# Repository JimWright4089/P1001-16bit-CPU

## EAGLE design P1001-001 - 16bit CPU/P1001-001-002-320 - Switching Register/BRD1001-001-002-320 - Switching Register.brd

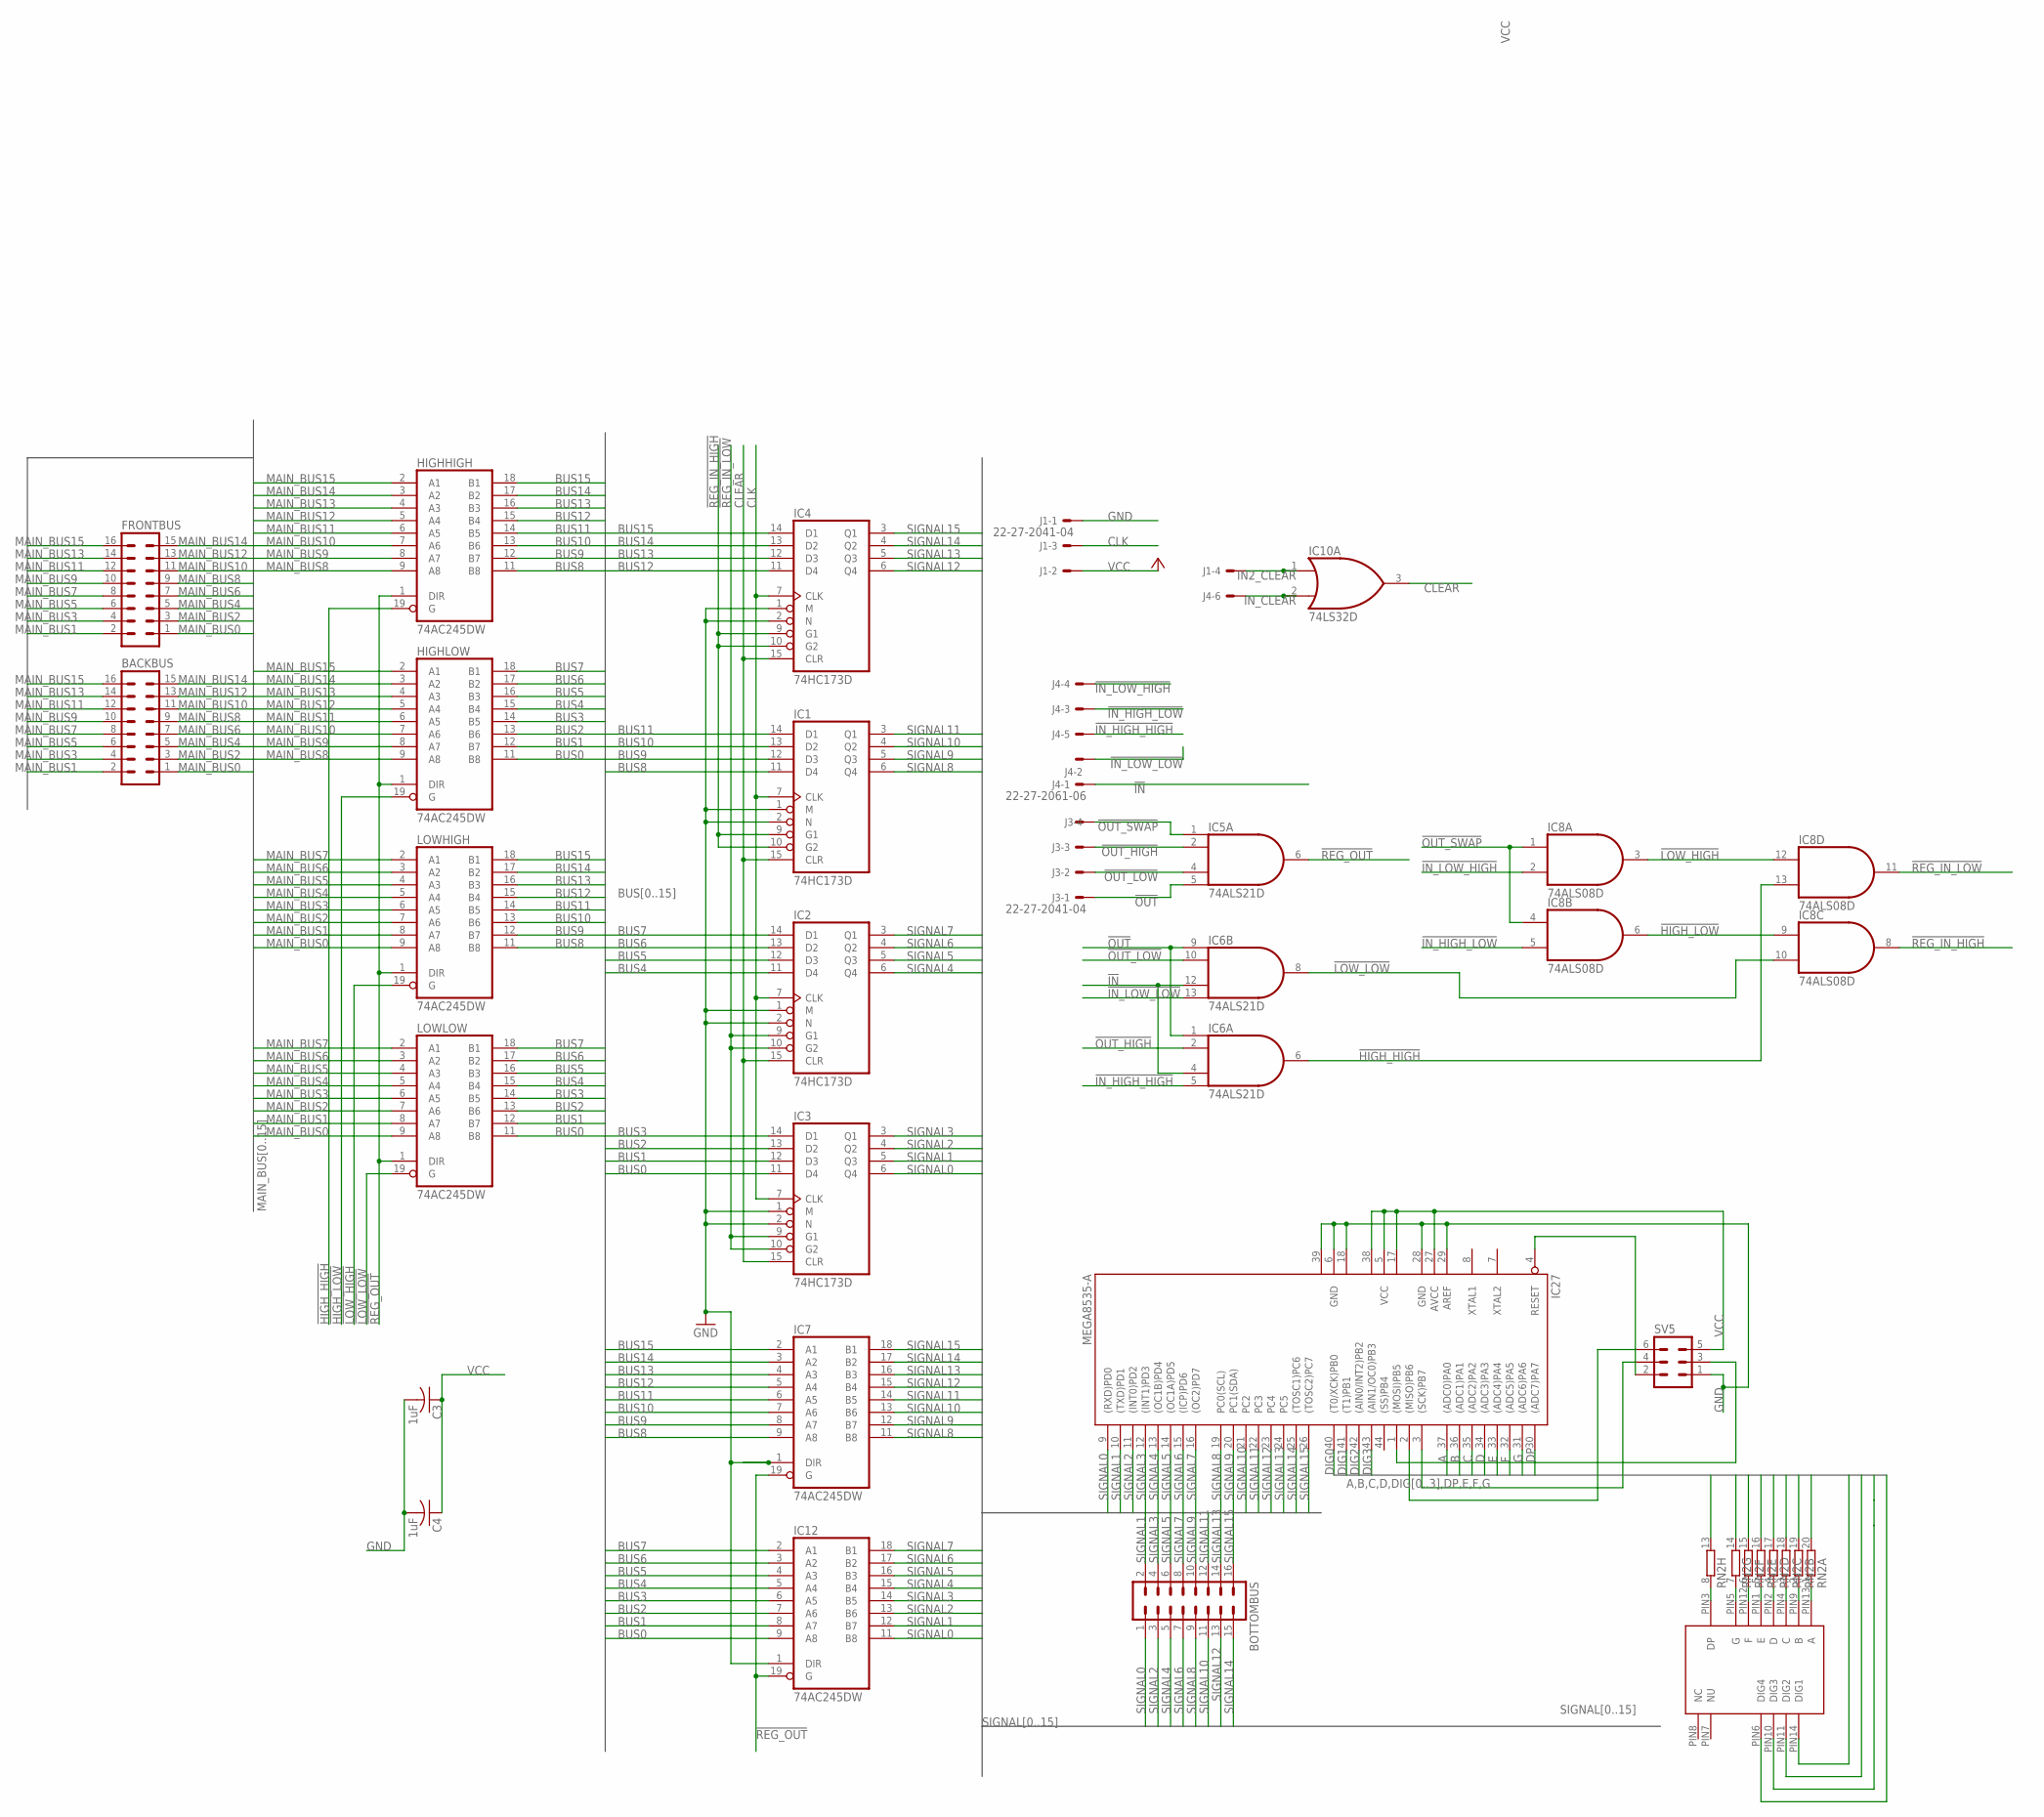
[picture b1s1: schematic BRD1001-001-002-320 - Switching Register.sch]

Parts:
BACKBUS: ML16
BOTTOMBUS: ML16
C3, C4: 1uF; C1206
FRONTBUS: ML16
HIGHHIGH: 74AC245DW; SO20W
HIGHLOW: 74AC245DW; SO20W
IC1, IC2, IC3, IC4: 74HC173D; SO16
IC5, IC6: 74ALS21D; SO14
IC7, IC12: 74AC245DW; SO20W
IC8: 74ALS08D; SO14
IC10: 74LS32D; SO14
IC27: MEGA8535-A; TQFP44
J1, J3: 22-27-2041-04; 6410-04
J4: 22-27-2061-06; 6410-06
LOWHIGH: 74AC245DW; SO20W
LOWLOW: 74AC245DW; SO20W
RN2: 10R-NSOMC; SOMC20
SV5: ML6
U$1: 4-DIGIT-7-SEGMENT

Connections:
!HIGH_HIGH: HIGHHIGH.19 (G), IC6.6 (O), IC8.13 (I1)
!HIGH_LOW: HIGHLOW.19 (G), IC8.6 (O), IC8.9 (I0)
!IN: IC6.4 (I2), IC6.12 (I2), J4.1
!IN_HIGH_HIGH: IC6.5 (I3), J4.5
!IN_HIGH_LOW: IC8.5 (I1), J4.3
!IN_LOW_HIGH: IC8.2 (I1), J4.4
!IN_LOW_LOW: IC6.13 (I3), J4.2
!LOW_HIGH: IC8.3 (O), IC8.12 (I0), LOWHIGH.19 (G)
!LOW_LOW: IC6.8 (O), IC8.10 (I1), LOWLOW.19 (G)
!OUT: IC5.5 (I3), IC6.1 (I0), IC6.9 (I0), J3.1
!OUT_HIGH: IC5.2 (I1), IC6.2 (I1), J3.3
!OUT_LOW: IC5.4 (I2), IC6.10 (I1), J3.2
!OUT_SWAP: IC5.1 (I0), IC8.1 (I0), IC8.4 (I0), J3.4
!REG_IN_HIGH: IC1.9 (G1), IC1.10 (G2), IC4.9 (G1), IC4.10 (G2), IC8.8 (O)
!REG_IN_LOW: IC2.9 (G1), IC2.10 (G2), IC3.9 (G1), IC3.10 (G2), IC8.11 (O)
!REG_OUT: HIGHHIGH.1 (DIR), HIGHLOW.1 (DIR), IC5.6 (O), IC7.19 (G), IC12.19 (G), LOWHIGH.1 (DIR), LOWLOW.1 (DIR)
A: IC27.37 ((ADC0)PA0), RN2.20 (2)
B: IC27.36 ((ADC1)PA1), RN2.19 (2)
BUS0: HIGHLOW.11 (B8), IC3.11 (D4), IC12.9 (A8), LOWLOW.11 (B8)
BUS1: HIGHLOW.12 (B7), IC3.12 (D3), IC12.8 (A7), LOWLOW.12 (B7)
BUS2: HIGHLOW.13 (B6), IC3.13 (D2), IC12.7 (A6), LOWLOW.13 (B6)
BUS3: HIGHLOW.14 (B5), IC3.14 (D1), IC12.6 (A5), LOWLOW.14 (B5)
BUS4: HIGHLOW.15 (B4), IC2.11 (D4), IC12.5 (A4), LOWLOW.15 (B4)
BUS5: HIGHLOW.16 (B3), IC2.12 (D3), IC12.4 (A3), LOWLOW.16 (B3)
BUS6: HIGHLOW.17 (B2), IC2.13 (D2), IC12.3 (A2), LOWLOW.17 (B2)
BUS7: HIGHLOW.18 (B1), IC2.14 (D1), IC12.2 (A1), LOWLOW.18 (B1)
BUS8: HIGHHIGH.11 (B8), IC1.11 (D4), IC7.9 (A8), LOWHIGH.11 (B8)
BUS9: HIGHHIGH.12 (B7), IC1.12 (D3), IC7.8 (A7), LOWHIGH.12 (B7)
BUS10: HIGHHIGH.13 (B6), IC1.13 (D2), IC7.7 (A6), LOWHIGH.13 (B6)
BUS11: HIGHHIGH.14 (B5), IC1.14 (D1), IC7.6 (A5), LOWHIGH.14 (B5)
BUS12: HIGHHIGH.15 (B4), IC4.11 (D4), IC7.5 (A4), LOWHIGH.15 (B4)
BUS13: HIGHHIGH.16 (B3), IC4.12 (D3), IC7.4 (A3), LOWHIGH.16 (B3)
BUS14: HIGHHIGH.17 (B2), IC4.13 (D2), IC7.3 (A2), LOWHIGH.17 (B2)
BUS15: HIGHHIGH.18 (B1), IC4.14 (D1), IC7.2 (A1), LOWHIGH.18 (B1)
C: IC27.35 ((ADC2)PA2), RN2.18 (2)
CLEAR: IC1.15 (CLR), IC2.15 (CLR), IC3.15 (CLR), IC4.15 (CLR), IC10.3 (O)
CLK: IC1.7 (CLK), IC2.7 (CLK), IC3.7 (CLK), IC4.7 (CLK), J1.3
D: IC27.34 ((ADC3)PA3), RN2.17 (2)
DIG0: IC27.40 ((T0/XCK)PB0), U$1.PIN14 (DIG1)
DIG1: IC27.41 ((T1)PB1), U$1.PIN11 (DIG2)
DIG2: IC27.42 ((AIN0/INT2)PB2), U$1.PIN10 (DIG3)
DIG3: IC27.43 ((AIN1/OC0)PB3), U$1.PIN6 (DIG4)
DP: IC27.30 ((ADC7)PA7), RN2.13 (2)
E: IC27.33 ((ADC4)PA4), RN2.16 (2)
F: IC27.32 ((ADC5)PA5), RN2.15 (2)
G: IC27.31 ((ADC6)PA6), RN2.14 (2)
GND: C3.2, C4.2, HIGHHIGH.10 (GND), HIGHLOW.10 (GND), IC1.1 (M), IC1.2 (N), IC1.8 (GND), IC2.1 (M), IC2.2 (N), IC2.8 (GND), IC3.1 (M), IC3.2 (N), IC3.8 (GND), IC4.1 (M), IC4.2 (N), IC4.8 (GND), IC5.7 (GND), IC6.7 (GND), IC7.1 (DIR), IC7.10 (GND), IC8.7 (GND), IC10.7 (GND), IC12.1 (DIR), IC12.10 (GND), IC27.6 (GND), IC27.18 (GND1), IC27.28 (GND), IC27.29 (AREF), IC27.39 (GND2), J1.1, LOWHIGH.10 (GND), LOWLOW.10 (GND), SV5.1
IN2_CLEAR: IC10.1 (I0), J1.4
IN_CLEAR: IC10.2 (I1), J4.6
MAIN_BUS0: BACKBUS.1, FRONTBUS.1, LOWHIGH.9 (A8), LOWLOW.9 (A8)
MAIN_BUS1: BACKBUS.2, FRONTBUS.2, LOWHIGH.8 (A7), LOWLOW.8 (A7)
MAIN_BUS2: BACKBUS.3, FRONTBUS.3, LOWHIGH.7 (A6), LOWLOW.7 (A6)
MAIN_BUS3: BACKBUS.4, FRONTBUS.4, LOWHIGH.6 (A5), LOWLOW.6 (A5)
MAIN_BUS4: BACKBUS.5, FRONTBUS.5, LOWHIGH.5 (A4), LOWLOW.5 (A4)
MAIN_BUS5: BACKBUS.6, FRONTBUS.6, LOWHIGH.4 (A3), LOWLOW.4 (A3)
MAIN_BUS6: BACKBUS.7, FRONTBUS.7, LOWHIGH.3 (A2), LOWLOW.3 (A2)
MAIN_BUS7: BACKBUS.8, FRONTBUS.8, LOWHIGH.2 (A1), LOWLOW.2 (A1)
MAIN_BUS8: BACKBUS.9, FRONTBUS.9, HIGHHIGH.9 (A8), HIGHLOW.9 (A8)
MAIN_BUS9: BACKBUS.10, FRONTBUS.10, HIGHHIGH.8 (A7), HIGHLOW.8 (A7)
MAIN_BUS10: BACKBUS.11, FRONTBUS.11, HIGHHIGH.7 (A6), HIGHLOW.7 (A6)
MAIN_BUS11: BACKBUS.12, FRONTBUS.12, HIGHHIGH.6 (A5), HIGHLOW.6 (A5)
MAIN_BUS12: BACKBUS.13, FRONTBUS.13, HIGHHIGH.5 (A4), HIGHLOW.5 (A4)
MAIN_BUS13: BACKBUS.14, FRONTBUS.14, HIGHHIGH.4 (A3), HIGHLOW.4 (A3)
MAIN_BUS14: BACKBUS.15, FRONTBUS.15, HIGHHIGH.3 (A2), HIGHLOW.3 (A2)
MAIN_BUS15: BACKBUS.16, FRONTBUS.16, HIGHHIGH.2 (A1), HIGHLOW.2 (A1)
unnamed: IC27.1 ((MOSI)PB5), SV5.3
unnamed: IC27.3 ((SCK)PB7), SV5.4
unnamed: IC27.2 ((MISO)PB6), SV5.6
unnamed: IC27.4 (RESET), SV5.2
unnamed: RN2.1, U$1.PIN13 (A)
unnamed: RN2.2 (1), U$1.PIN9 (B)
unnamed: RN2.3 (1), U$1.PIN4 (C)
unnamed: RN2.4 (1), U$1.PIN2 (D)
unnamed: RN2.5 (1), U$1.PIN1 (E)
unnamed: RN2.6 (1), U$1.PIN12 (F)
unnamed: RN2.7 (1), U$1.PIN5 (G)
unnamed: RN2.8 (1), U$1.PIN3 (DP)
SIGNAL0: BOTTOMBUS.1, IC3.6 (Q4), IC12.11 (B8), IC27.9 ((RXD)PD0)
SIGNAL1: BOTTOMBUS.2, IC3.5 (Q3), IC12.12 (B7), IC27.10 ((TXD)PD1)
SIGNAL2: BOTTOMBUS.3, IC3.4 (Q2), IC12.13 (B6), IC27.11 ((INT0)PD2)
SIGNAL3: BOTTOMBUS.4, IC3.3 (Q1), IC12.14 (B5), IC27.12 ((INT1)PD3)
SIGNAL4: BOTTOMBUS.5, IC2.6 (Q4), IC12.15 (B4), IC27.13 ((OC1B)PD4)
SIGNAL5: BOTTOMBUS.6, IC2.5 (Q3), IC12.16 (B3), IC27.14 ((OC1A)PD5)
SIGNAL6: BOTTOMBUS.7, IC2.4 (Q2), IC12.17 (B2), IC27.15 ((ICP)PD6)
SIGNAL7: BOTTOMBUS.8, IC2.3 (Q1), IC12.18 (B1), IC27.16 ((OC2)PD7)
SIGNAL8: BOTTOMBUS.9, IC1.6 (Q4), IC7.11 (B8), IC27.19 (PC0(SCL))
SIGNAL9: BOTTOMBUS.10, IC1.5 (Q3), IC7.12 (B7), IC27.20 (PC1(SDA))
SIGNAL10: BOTTOMBUS.11, IC1.4 (Q2), IC7.13 (B6), IC27.21 (PC2)
SIGNAL11: BOTTOMBUS.12, IC1.3 (Q1), IC7.14 (B5), IC27.22 (PC3)
SIGNAL12: BOTTOMBUS.13, IC4.6 (Q4), IC7.15 (B4), IC27.23 (PC4)
SIGNAL13: BOTTOMBUS.14, IC4.5 (Q3), IC7.16 (B3), IC27.24 (PC5)
SIGNAL14: BOTTOMBUS.15, IC4.4 (Q2), IC7.17 (B2), IC27.25 ((TOSC1)PC6)
SIGNAL15: BOTTOMBUS.16, IC4.3 (Q1), IC7.18 (B1), IC27.26 ((TOSC2)PC7)
VCC: C3.1, C4.1, HIGHHIGH.20 (VCC), HIGHLOW.20 (VCC), IC1.16 (VCC), IC2.16 (VCC), IC3.16 (VCC), IC4.16 (VCC), IC5.14 (VCC), IC6.14 (VCC), IC7.20 (VCC), IC8.14 (VCC), IC10.14 (VCC), IC12.20 (VCC), IC27.5 (VCC), IC27.17 (VCC1), IC27.27 (AVCC), IC27.38 (VCC2), J1.2, LOWHIGH.20 (VCC), LOWLOW.20 (VCC), SV5.5

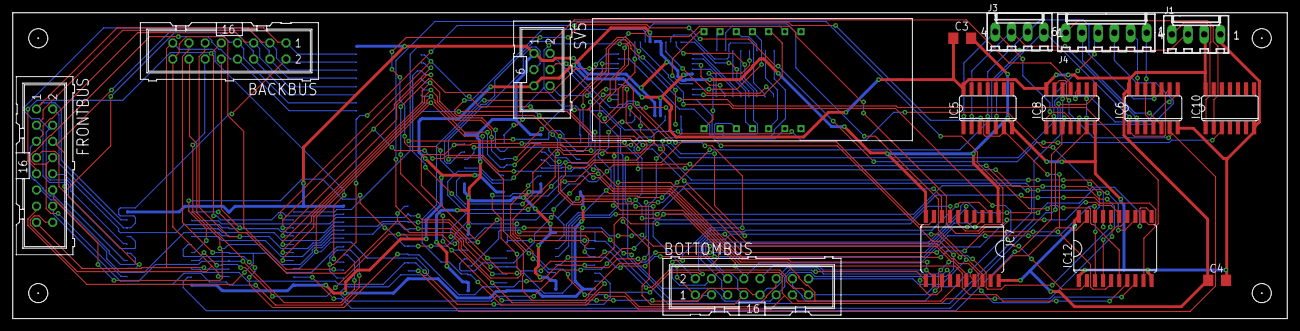
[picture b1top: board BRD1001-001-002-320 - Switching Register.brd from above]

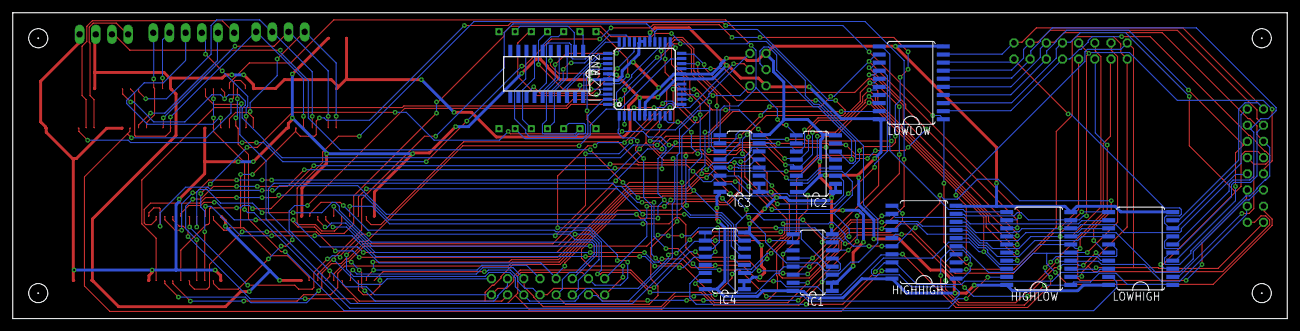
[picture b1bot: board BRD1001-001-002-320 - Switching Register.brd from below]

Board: 2 copper layers, 200.0 x 48.0 mm, 26 parts (10 on the bottom side), 94 nets.

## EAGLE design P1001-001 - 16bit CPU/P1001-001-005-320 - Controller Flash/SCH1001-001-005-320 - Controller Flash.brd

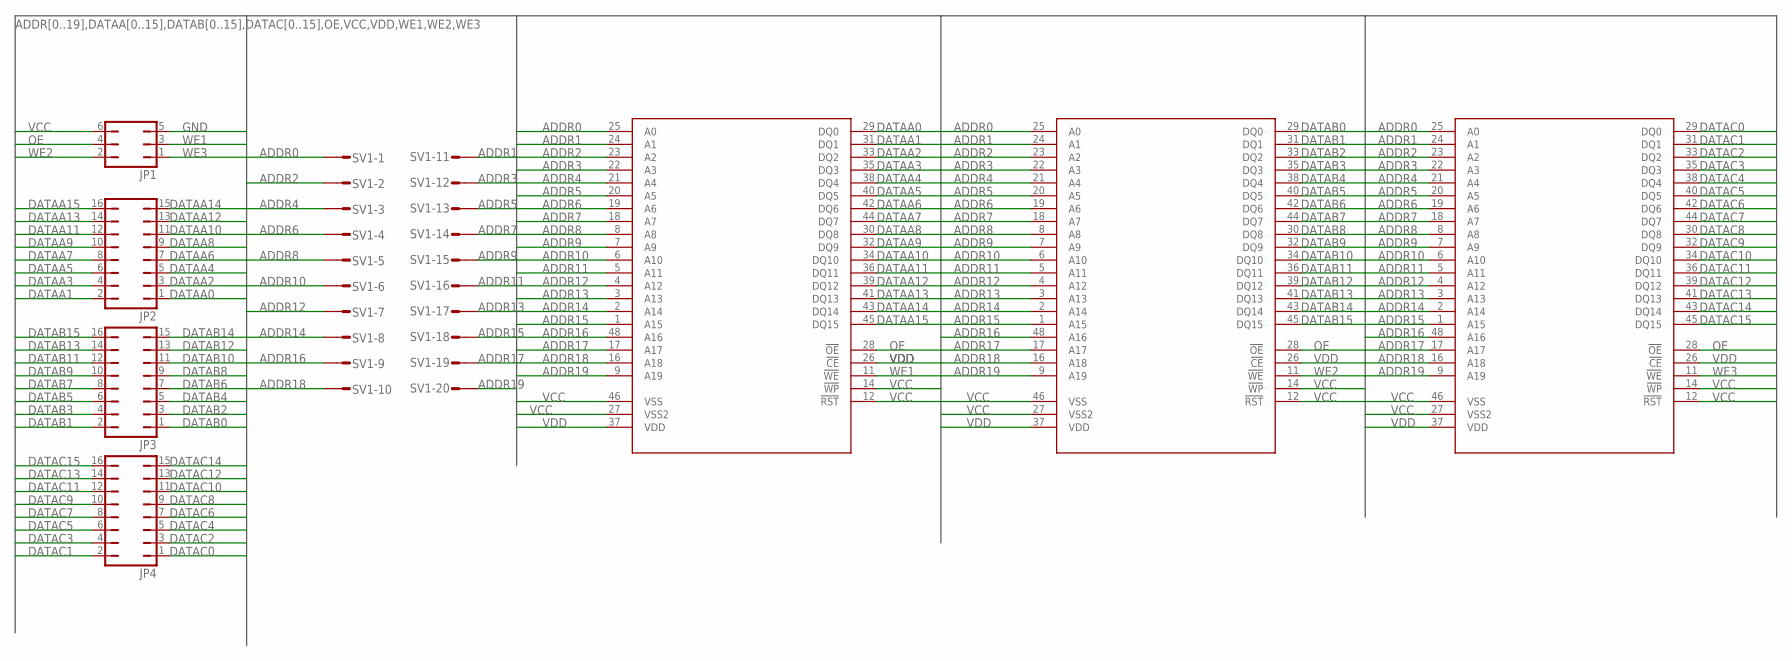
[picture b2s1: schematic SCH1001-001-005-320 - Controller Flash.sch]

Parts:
JP1: JP3Q
JP2, JP3, JP4: JP8Q
SV1: S20P
U$1, U$2, U$3: SST39VF1602-70-4I-EKE; TSOP48

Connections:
ADDR0: SV1.1, U$1.25 (A0), U$2.25 (A0), U$3.25 (A0)
ADDR1: SV1.11, U$1.24 (A1), U$2.24 (A1), U$3.24 (A1)
ADDR2: SV1.2, U$1.23 (A2), U$2.23 (A2), U$3.23 (A2)
ADDR3: SV1.12, U$1.22 (A3), U$2.22 (A3), U$3.22 (A3)
ADDR4: SV1.3, U$1.21 (A4), U$2.21 (A4), U$3.21 (A4)
ADDR5: SV1.13, U$1.20 (A5), U$2.20 (A5), U$3.20 (A5)
ADDR6: SV1.4, U$1.19 (A6), U$2.19 (A6), U$3.19 (A6)
ADDR7: SV1.14, U$1.18 (A7), U$2.18 (A7), U$3.18 (A7)
ADDR8: SV1.5, U$1.8 (A8), U$2.8 (A8), U$3.8 (A8)
ADDR9: SV1.15, U$1.7 (A9), U$2.7 (A9), U$3.7 (A9)
ADDR10: SV1.6, U$1.6 (A10), U$2.6 (A10), U$3.6 (A10)
ADDR11: SV1.16, U$1.5 (A11), U$2.5 (A11), U$3.5 (A11)
ADDR12: SV1.7, U$1.4 (A12), U$2.4 (A12), U$3.4 (A12)
ADDR13: SV1.17, U$1.3 (A13), U$2.3 (A13), U$3.3 (A13)
ADDR14: SV1.8, U$1.2 (A14), U$2.2 (A14), U$3.2 (A14)
ADDR15: SV1.18, U$1.1 (A15), U$2.1 (A15), U$3.1 (A15)
ADDR16: SV1.9, U$1.48 (A16), U$2.48 (A16), U$3.48 (A16)
ADDR17: SV1.19, U$1.17 (A17), U$2.17 (A17), U$3.17 (A17)
ADDR18: SV1.10, U$1.16 (A18), U$2.16 (A18), U$3.16 (A18)
ADDR19: SV1.20, U$1.9 (A19), U$2.9 (A19), U$3.9 (A19)
DATAA0: JP2.1, U$1.29 (DQ0)
DATAA1: JP2.2, U$1.31 (DQ1)
DATAA2: JP2.3, U$1.33 (DQ2)
DATAA3: JP2.4, U$1.35 (DQ3)
DATAA4: JP2.5, U$1.38 (DQ4)
DATAA5: JP2.6, U$1.40 (DQ5)
DATAA6: JP2.7, U$1.42 (DQ6)
DATAA7: JP2.8, U$1.44 (DQ7)
DATAA8: JP2.9, U$1.30 (DQ8)
DATAA9: JP2.10, U$1.32 (DQ9)
DATAA10: JP2.11, U$1.34 (DQ10)
DATAA11: JP2.12, U$1.36 (DQ11)
DATAA12: JP2.13, U$1.39 (DQ12)
DATAA13: JP2.14, U$1.41 (DQ13)
DATAA14: JP2.15, U$1.43 (DQ14)
DATAA15: JP2.16, U$1.45 (DQ15)
DATAB0: JP3.1, U$2.29 (DQ0)
DATAB1: JP3.2, U$2.31 (DQ1)
DATAB2: JP3.3, U$2.33 (DQ2)
DATAB3: JP3.4, U$2.35 (DQ3)
DATAB4: JP3.5, U$2.38 (DQ4)
DATAB5: JP3.6, U$2.40 (DQ5)
DATAB6: JP3.7, U$2.42 (DQ6)
DATAB7: JP3.8, U$2.44 (DQ7)
DATAB8: JP3.9, U$2.30 (DQ8)
DATAB9: JP3.10, U$2.32 (DQ9)
DATAB10: JP3.11, U$2.34 (DQ10)
DATAB11: JP3.12, U$2.36 (DQ11)
DATAB12: JP3.13, U$2.39 (DQ12)
DATAB13: JP3.14, U$2.41 (DQ13)
DATAB14: JP3.15, U$2.43 (DQ14)
DATAB15: JP3.16, U$2.45 (DQ15)
DATAC0: JP4.1, U$3.29 (DQ0)
DATAC1: JP4.2, U$3.31 (DQ1)
DATAC2: JP4.3, U$3.33 (DQ2)
DATAC3: JP4.4, U$3.35 (DQ3)
DATAC4: JP4.5, U$3.38 (DQ4)
DATAC5: JP4.6, U$3.40 (DQ5)
DATAC6: JP4.7, U$3.42 (DQ6)
DATAC7: JP4.8, U$3.44 (DQ7)
DATAC8: JP4.9, U$3.30 (DQ8)
DATAC9: JP4.10, U$3.32 (DQ9)
DATAC10: JP4.11, U$3.34 (DQ10)
DATAC11: JP4.12, U$3.36 (DQ11)
DATAC12: JP4.13, U$3.39 (DQ12)
DATAC13: JP4.14, U$3.41 (DQ13)
DATAC14: JP4.15, U$3.43 (DQ14)
DATAC15: JP4.16, U$3.45 (DQ15)
GND: JP1.5
OE: JP1.4, U$1.28 (!OE), U$2.28 (!OE), U$3.28 (!OE)
VCC: JP1.6, U$1.12 (!RST), U$1.14 (!WP), U$1.27 (VSS2), U$1.46 (VSS), U$2.12 (!RST), U$2.14 (!WP), U$2.27 (VSS2), U$2.46 (VSS), U$3.12 (!RST), U$3.14 (!WP), U$3.27 (VSS2), U$3.46 (VSS)
VDD: U$1.26 (!CE), U$1.37 (VDD), U$2.26 (!CE), U$2.37 (VDD), U$3.26 (!CE), U$3.37 (VDD)
WE1: JP1.3, U$1.11 (!WE)
WE2: JP1.2, U$2.11 (!WE)
WE3: JP1.1, U$3.11 (!WE)

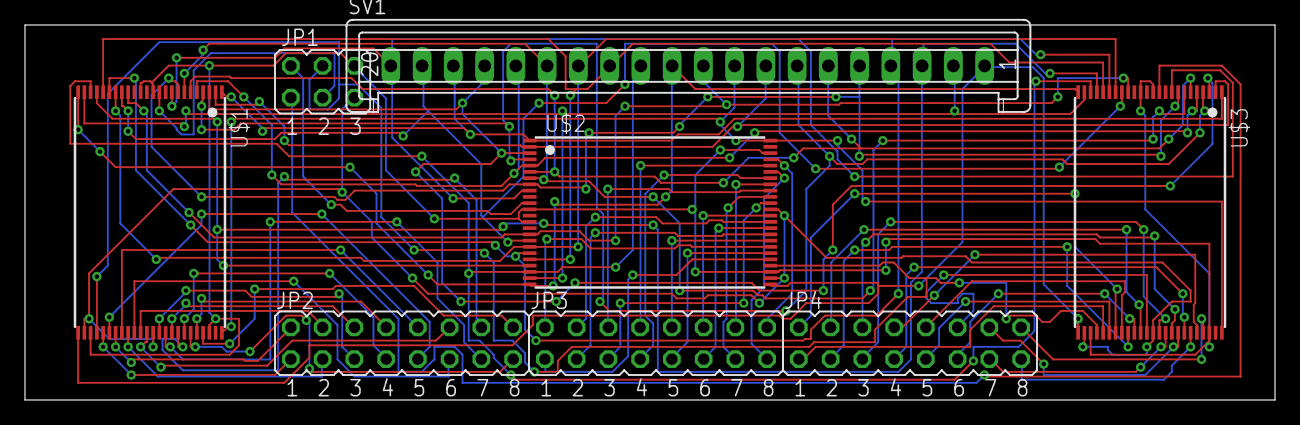
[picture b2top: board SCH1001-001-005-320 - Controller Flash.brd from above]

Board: 2 copper layers, 100.0 x 30.0 mm, 8 parts (0 on the bottom side), 74 nets.

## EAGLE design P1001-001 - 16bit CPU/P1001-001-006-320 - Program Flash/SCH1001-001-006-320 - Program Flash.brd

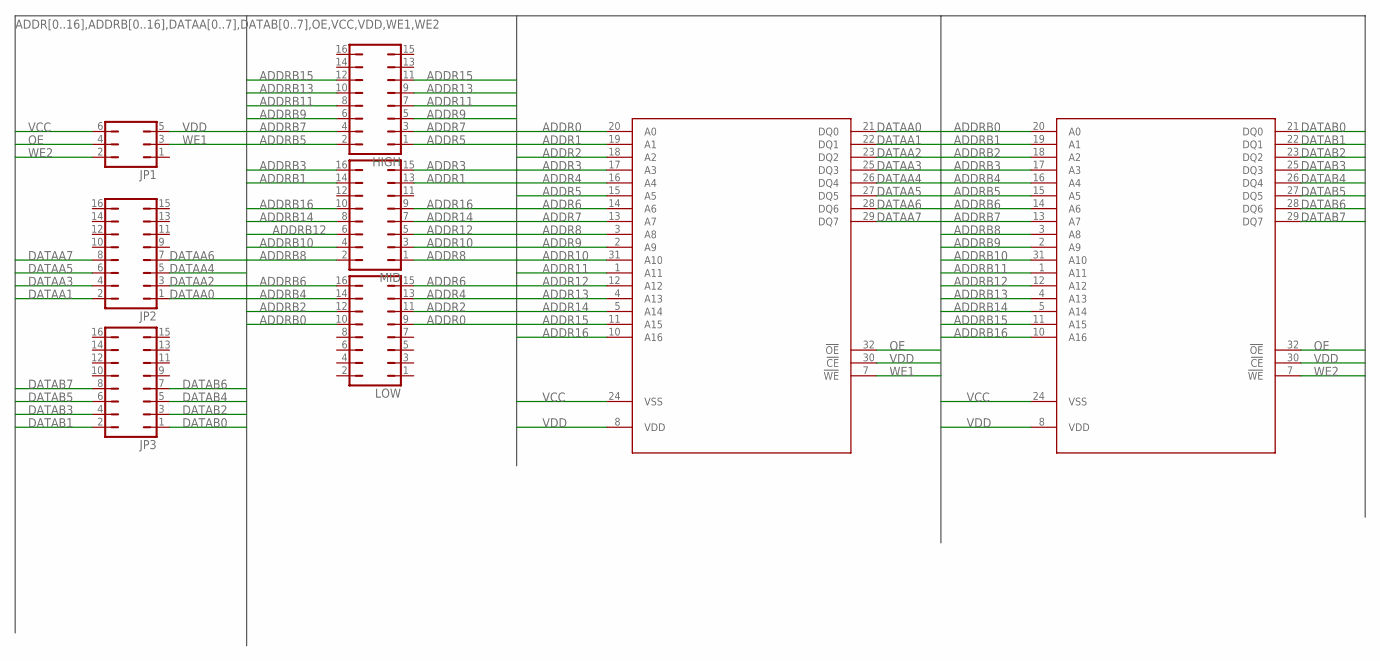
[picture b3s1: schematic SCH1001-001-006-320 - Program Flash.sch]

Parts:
HIGH: JP8Q
JP1: JP3Q
JP2, JP3: JP8Q
LOW: JP8Q
MID: JP8Q
U$1, U$2: PROGRAMFLASH; TSOP32

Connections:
ADDR0: LOW.9, U$1.20 (A0)
ADDR1: MID.13, U$1.19 (A1)
ADDR2: LOW.11, U$1.18 (A2)
ADDR3: MID.15, U$1.17 (A3)
ADDR4: LOW.13, U$1.16 (A4)
ADDR5: HIGH.1, U$1.15 (A5)
ADDR6: LOW.15, U$1.14 (A6)
ADDR7: HIGH.3, U$1.13 (A7)
ADDR8: MID.1, U$1.3 (A8)
ADDR9: HIGH.5, U$1.2 (A9)
ADDR10: MID.3, U$1.31 (A10)
ADDR11: HIGH.7, U$1.1 (A11)
ADDR12: MID.5, U$1.12 (A12)
ADDR13: HIGH.9, U$1.4 (A13)
ADDR14: MID.7, U$1.5 (A14)
ADDR15: HIGH.11, U$1.11 (A15)
ADDR16: MID.9, U$1.10 (A16)
ADDRB0: LOW.10, U$2.20 (A0)
ADDRB1: MID.14, U$2.19 (A1)
ADDRB2: LOW.12, U$2.18 (A2)
ADDRB3: MID.16, U$2.17 (A3)
ADDRB4: LOW.14, U$2.16 (A4)
ADDRB5: HIGH.2, U$2.15 (A5)
ADDRB6: LOW.16, U$2.14 (A6)
ADDRB7: HIGH.4, U$2.13 (A7)
ADDRB8: MID.2, U$2.3 (A8)
ADDRB9: HIGH.6, U$2.2 (A9)
ADDRB10: MID.4, U$2.31 (A10)
ADDRB11: HIGH.8, U$2.1 (A11)
ADDRB12: MID.6, U$2.12 (A12)
ADDRB13: HIGH.10, U$2.4 (A13)
ADDRB14: MID.8, U$2.5 (A14)
ADDRB15: HIGH.12, U$2.11 (A15)
ADDRB16: MID.10, U$2.10 (A16)
DATAA0: JP2.1, U$1.21 (DQ0)
DATAA1: JP2.2, U$1.22 (DQ1)
DATAA2: JP2.3, U$1.23 (DQ2)
DATAA3: JP2.4, U$1.25 (DQ3)
DATAA4: JP2.5, U$1.26 (DQ4)
DATAA5: JP2.6, U$1.27 (DQ5)
DATAA6: JP2.7, U$1.28 (DQ6)
DATAA7: JP2.8, U$1.29 (DQ7)
DATAB0: JP3.1, U$2.21 (DQ0)
DATAB1: JP3.2, U$2.22 (DQ1)
DATAB2: JP3.3, U$2.23 (DQ2)
DATAB3: JP3.4, U$2.25 (DQ3)
DATAB4: JP3.5, U$2.26 (DQ4)
DATAB5: JP3.6, U$2.27 (DQ5)
DATAB6: JP3.7, U$2.28 (DQ6)
DATAB7: JP3.8, U$2.29 (DQ7)
OE: JP1.4, U$1.32 (!OE), U$2.32 (!OE)
VCC: JP1.6, U$1.24 (VSS), U$2.24 (VSS)
VDD: JP1.5, U$1.8 (VDD), U$1.30 (!CE), U$2.8 (VDD), U$2.30 (!CE)
WE1: JP1.3, U$1.7 (!WE)
WE2: JP1.2, U$2.7 (!WE)

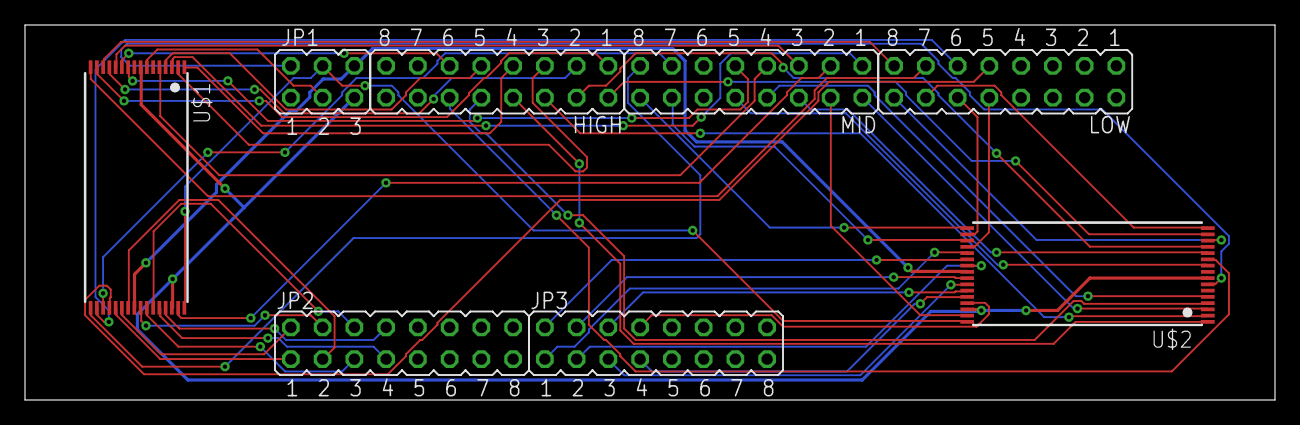
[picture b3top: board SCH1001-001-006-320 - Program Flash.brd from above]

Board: 2 copper layers, 100.0 x 30.0 mm, 8 parts (0 on the bottom side), 55 nets.

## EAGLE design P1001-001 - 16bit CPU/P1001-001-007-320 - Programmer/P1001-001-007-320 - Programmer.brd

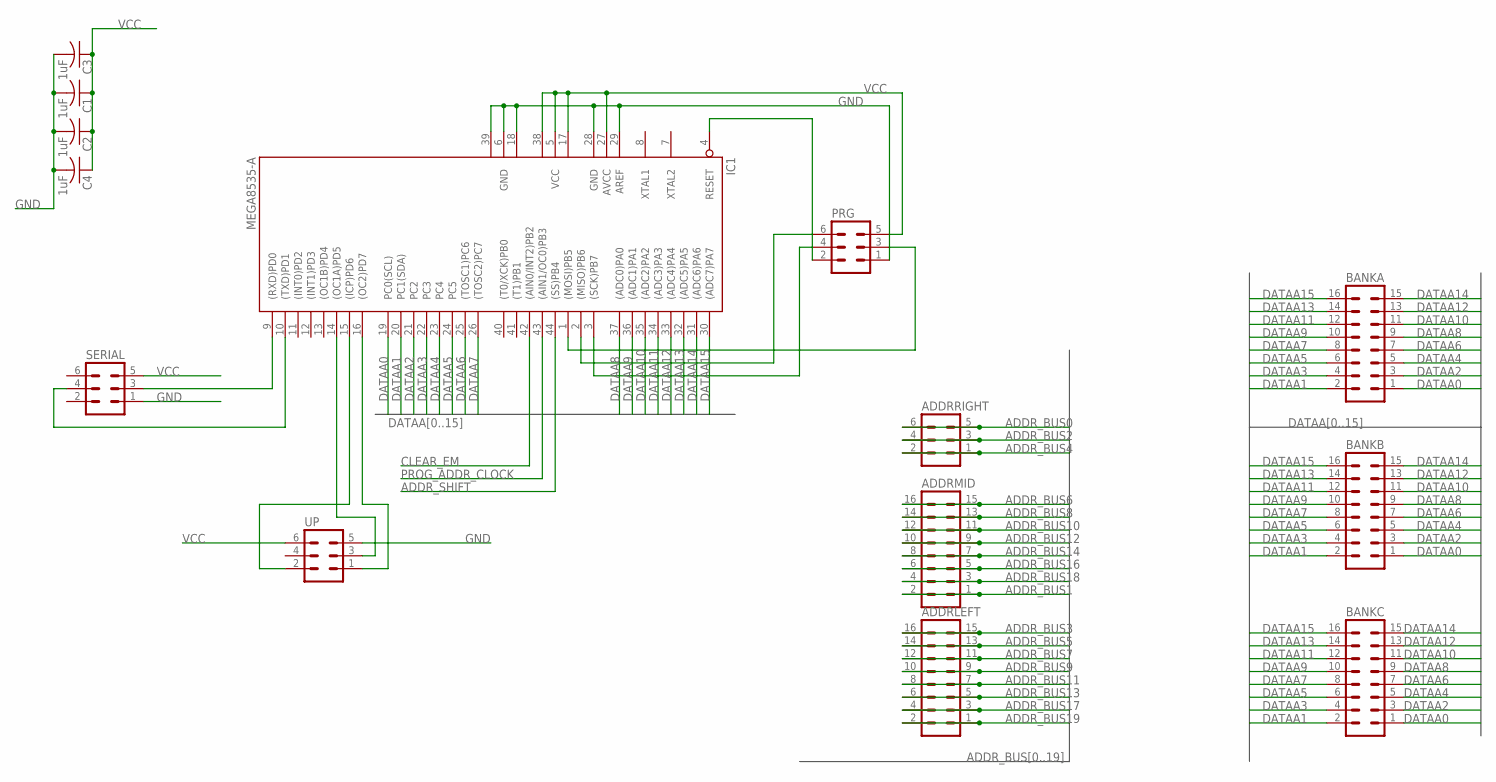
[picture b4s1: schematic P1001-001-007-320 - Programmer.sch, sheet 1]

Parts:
ADDRLEFT: ML16
ADDRMID: ML16
ADDRRIGHT: ML6
BANKA: ML16
BANKB: ML16
BANKC: ML16
C1, C2, C3, C4: 1uF; C1206
IC1: MEGA8535-A; TQFP44
PRG: ML6
SERIAL: ML6
UP: ML6

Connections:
ADDR_BUS0: ADDRRIGHT.5, ADDRRIGHT.6; also elsewhere on the board
ADDR_BUS1: ADDRMID.1, ADDRMID.2; also elsewhere on the board
ADDR_BUS2: ADDRRIGHT.3, ADDRRIGHT.4; also elsewhere on the board
ADDR_BUS3: ADDRLEFT.15, ADDRLEFT.16; also elsewhere on the board
ADDR_BUS4: ADDRRIGHT.1, ADDRRIGHT.2; also elsewhere on the board
ADDR_BUS5: ADDRLEFT.13, ADDRLEFT.14; also elsewhere on the board
ADDR_BUS6: ADDRMID.15, ADDRMID.16; also elsewhere on the board
ADDR_BUS7: ADDRLEFT.11, ADDRLEFT.12; also elsewhere on the board
ADDR_BUS8: ADDRMID.13, ADDRMID.14; also elsewhere on the board
ADDR_BUS9: ADDRLEFT.9, ADDRLEFT.10; also elsewhere on the board
ADDR_BUS10: ADDRMID.11, ADDRMID.12; also elsewhere on the board
ADDR_BUS11: ADDRLEFT.7, ADDRLEFT.8; also elsewhere on the board
ADDR_BUS12: ADDRMID.9, ADDRMID.10; also elsewhere on the board
ADDR_BUS13: ADDRLEFT.5, ADDRLEFT.6; also elsewhere on the board
ADDR_BUS14: ADDRMID.7, ADDRMID.8; also elsewhere on the board
ADDR_BUS16: ADDRMID.5, ADDRMID.6; also elsewhere on the board
ADDR_BUS17: ADDRLEFT.3, ADDRLEFT.4; also elsewhere on the board
ADDR_BUS18: ADDRMID.3, ADDRMID.4; also elsewhere on the board
ADDR_BUS19: ADDRLEFT.1, ADDRLEFT.2; also elsewhere on the board
ADDR_SHIFT: IC1.44 ((SS)PB4); also elsewhere on the board
CLEAR_EM: IC1.42 ((AIN0/INT2)PB2); also elsewhere on the board
DATAA0: BANKA.1, BANKB.1, BANKC.1, IC1.19 (PC0(SCL))
DATAA1: BANKA.2, BANKB.2, BANKC.2, IC1.20 (PC1(SDA))
DATAA2: BANKA.3, BANKB.3, BANKC.3, IC1.21 (PC2)
DATAA3: BANKA.4, BANKB.4, BANKC.4, IC1.22 (PC3)
DATAA4: BANKA.5, BANKB.5, BANKC.5, IC1.23 (PC4)
DATAA5: BANKA.6, BANKB.6, BANKC.6, IC1.24 (PC5)
DATAA6: BANKA.7, BANKB.7, BANKC.7, IC1.25 ((TOSC1)PC6)
DATAA7: BANKA.8, BANKB.8, BANKC.8, IC1.26 ((TOSC2)PC7)
DATAA8: BANKA.9, BANKB.9, BANKC.9, IC1.37 ((ADC0)PA0)
DATAA9: BANKA.10, BANKB.10, BANKC.10, IC1.36 ((ADC1)PA1)
DATAA10: BANKA.11, BANKB.11, BANKC.11, IC1.35 ((ADC2)PA2)
DATAA11: BANKA.12, BANKB.12, BANKC.12, IC1.34 ((ADC3)PA3)
DATAA12: BANKA.13, BANKB.13, BANKC.13, IC1.33 ((ADC4)PA4)
DATAA13: BANKA.14, BANKB.14, BANKC.14, IC1.32 ((ADC5)PA5)
DATAA14: BANKA.15, BANKB.15, BANKC.15, IC1.31 ((ADC6)PA6)
DATAA15: BANKA.16, BANKB.16, BANKC.16, IC1.30 ((ADC7)PA7)
GND: C1.2, C2.2, C3.2, C4.2, IC1.6 (GND), IC1.18 (GND1), IC1.28 (GND), IC1.29 (AREF), IC1.39 (GND2), PRG.1, SERIAL.1, UP.5; also elsewhere on the board
unnamed: IC1.14 ((OC1A)PD5), UP.3
unnamed: IC1.1 ((MOSI)PB5), PRG.3
unnamed: IC1.3 ((SCK)PB7), PRG.4
unnamed: IC1.2 ((MISO)PB6), PRG.6
unnamed: IC1.4 (RESET), PRG.2
unnamed: IC1.16 ((OC2)PD7), UP.1
unnamed: IC1.9 ((RXD)PD0), SERIAL.3
unnamed: IC1.10 ((TXD)PD1), SERIAL.4
unnamed: IC1.15 ((ICP)PD6), UP.2
PROG_ADDR_CLOCK: IC1.43 ((AIN1/OC0)PB3); also elsewhere on the board
VCC: C1.1, C2.1, C3.1, C4.1, IC1.5 (VCC), IC1.17 (VCC1), IC1.27 (AVCC), IC1.38 (VCC2), PRG.5, SERIAL.5, UP.6; also elsewhere on the board

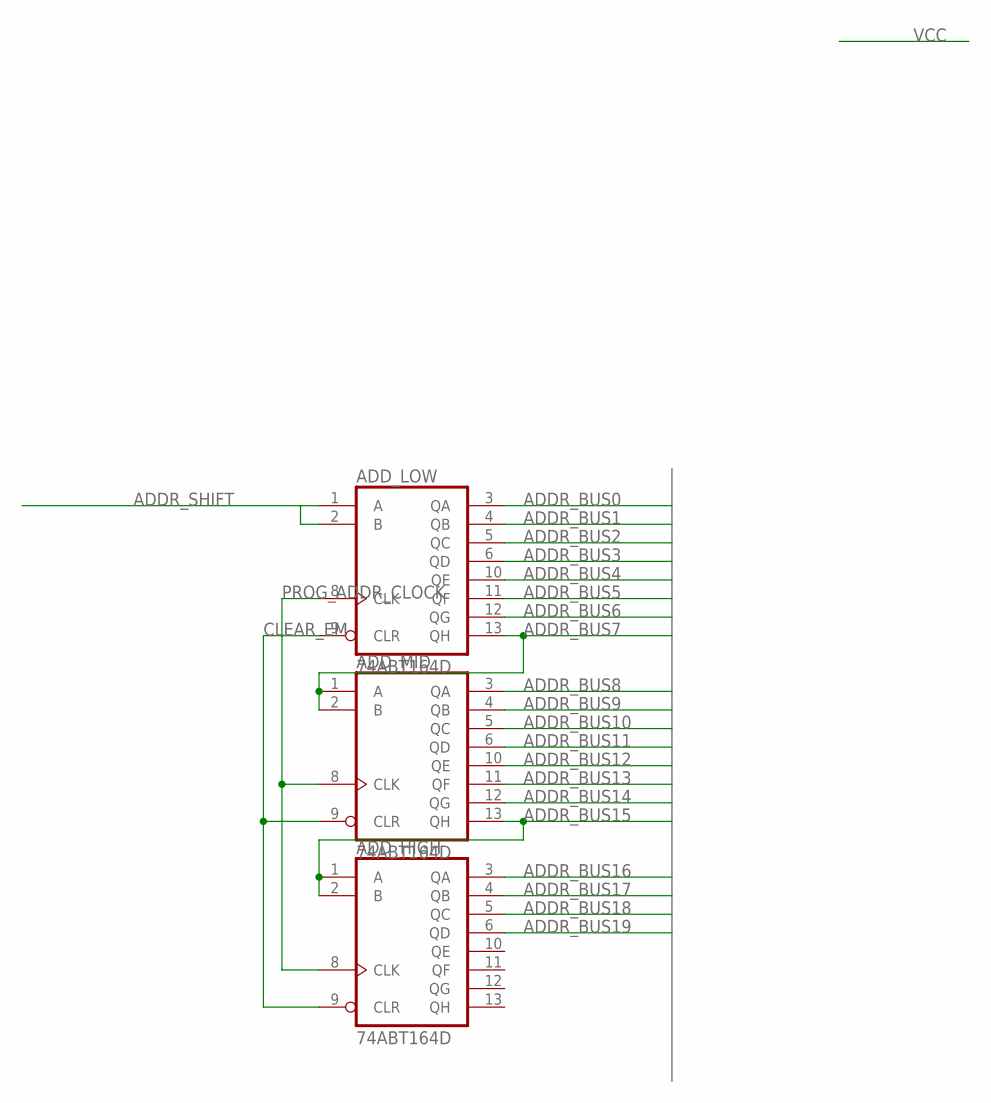
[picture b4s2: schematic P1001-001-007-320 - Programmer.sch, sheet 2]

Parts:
ADD_HIGH: 74ABT164D; SO14
ADD_LOW: 74ABT164D; SO14
ADD_MID: 74ABT164D; SO14

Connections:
ADDR_BUS0: ADD_LOW.3 (QA); also elsewhere on the board
ADDR_BUS1: ADD_LOW.4 (QB); also elsewhere on the board
ADDR_BUS2: ADD_LOW.5 (QC); also elsewhere on the board
ADDR_BUS3: ADD_LOW.6 (QD); also elsewhere on the board
ADDR_BUS4: ADD_LOW.10 (QE); also elsewhere on the board
ADDR_BUS5: ADD_LOW.11 (QF); also elsewhere on the board
ADDR_BUS6: ADD_LOW.12 (QG); also elsewhere on the board
ADDR_BUS7: ADD_LOW.13 (QH), ADD_MID.1 (A), ADD_MID.2 (B); also elsewhere on the board
ADDR_BUS8: ADD_MID.3 (QA); also elsewhere on the board
ADDR_BUS9: ADD_MID.4 (QB); also elsewhere on the board
ADDR_BUS10: ADD_MID.5 (QC); also elsewhere on the board
ADDR_BUS11: ADD_MID.6 (QD); also elsewhere on the board
ADDR_BUS12: ADD_MID.10 (QE); also elsewhere on the board
ADDR_BUS13: ADD_MID.11 (QF); also elsewhere on the board
ADDR_BUS14: ADD_MID.12 (QG); also elsewhere on the board
ADDR_BUS15: ADD_HIGH.1 (A), ADD_HIGH.2 (B), ADD_MID.13 (QH)
ADDR_BUS16: ADD_HIGH.3 (QA); also elsewhere on the board
ADDR_BUS17: ADD_HIGH.4 (QB); also elsewhere on the board
ADDR_BUS18: ADD_HIGH.5 (QC); also elsewhere on the board
ADDR_BUS19: ADD_HIGH.6 (QD); also elsewhere on the board
ADDR_SHIFT: ADD_LOW.1 (A), ADD_LOW.2 (B); also elsewhere on the board
CLEAR_EM: ADD_HIGH.9 (CLR), ADD_LOW.9 (CLR), ADD_MID.9 (CLR); also elsewhere on the board
GND: ADD_HIGH.7 (GND), ADD_LOW.7 (GND), ADD_MID.7 (GND); also elsewhere on the board
PROG_ADDR_CLOCK: ADD_HIGH.8 (CLK), ADD_LOW.8 (CLK), ADD_MID.8 (CLK); also elsewhere on the board
VCC: ADD_HIGH.14 (VCC), ADD_LOW.14 (VCC), ADD_MID.14 (VCC); also elsewhere on the board

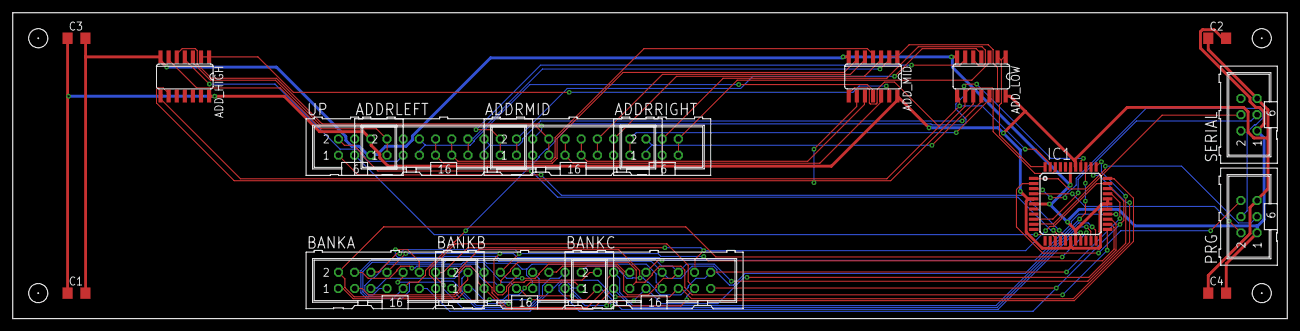
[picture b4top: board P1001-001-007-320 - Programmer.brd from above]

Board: 2 copper layers, 200.0 x 48.0 mm, 17 parts (0 on the bottom side), 50 nets.

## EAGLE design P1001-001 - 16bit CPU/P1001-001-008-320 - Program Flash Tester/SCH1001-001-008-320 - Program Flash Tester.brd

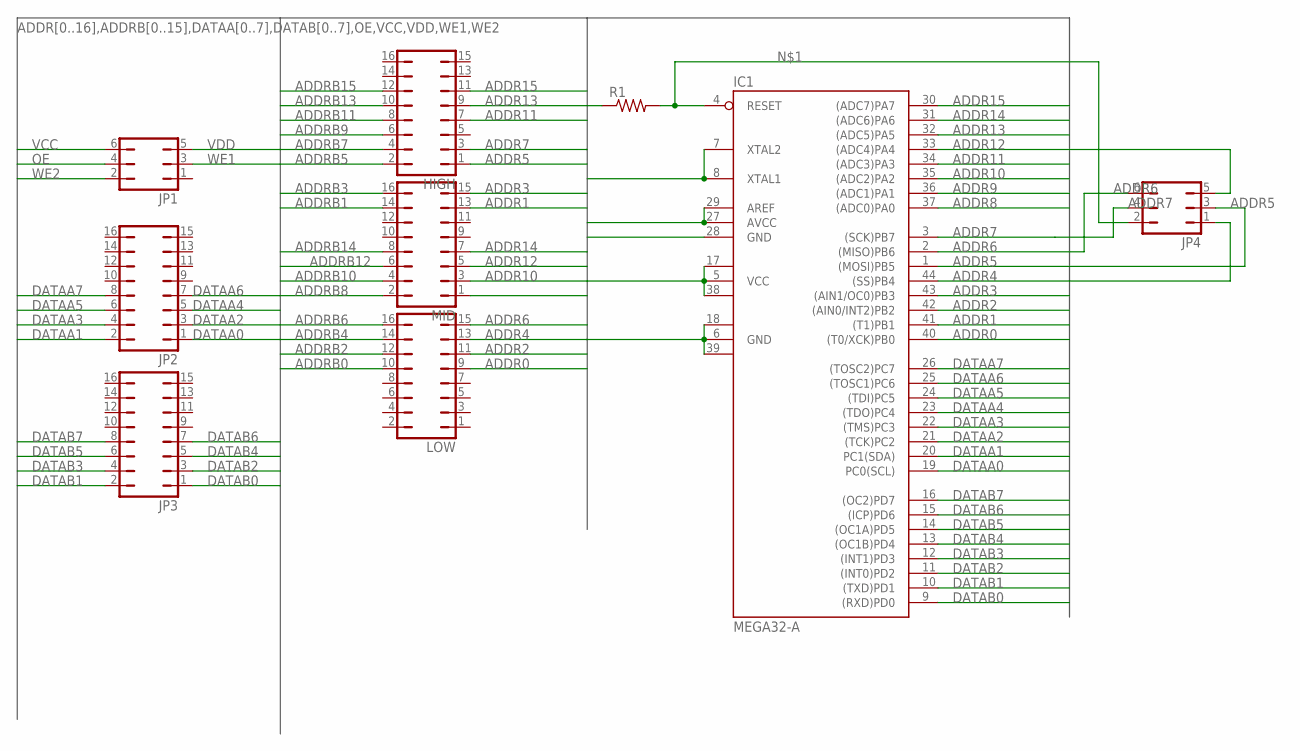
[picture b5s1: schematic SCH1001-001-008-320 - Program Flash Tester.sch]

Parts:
HIGH: JP8Q
IC1: MEGA32-A; TQFP44
JP1, JP4: JP3Q
JP2, JP3: JP8Q
LOW: JP8Q
MID: JP8Q
R1: R-US_M1206; M1206

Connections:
ADDR0: IC1.40 ((T0/XCK)PB0), LOW.9
ADDR1: IC1.41 ((T1)PB1), MID.13
ADDR2: IC1.42 ((AIN0/INT2)PB2), LOW.11
ADDR3: IC1.43 ((AIN1/OC0)PB3), MID.15
ADDR4: IC1.44 ((SS)PB4), LOW.13
ADDR5: HIGH.1, IC1.1 ((MOSI)PB5), JP4.3
ADDR6: IC1.2 ((MISO)PB6), JP4.6, LOW.15
ADDR7: HIGH.3, IC1.3 ((SCK)PB7), JP4.4
ADDR8: IC1.37 ((ADC0)PA0), MID.1
ADDR9: IC1.36 ((ADC1)PA1)
ADDR10: IC1.35 ((ADC2)PA2), MID.3
ADDR11: HIGH.7, IC1.34 ((ADC3)PA3)
ADDR12: IC1.33 ((ADC4)PA4), MID.5
ADDR13: HIGH.9, IC1.32 ((ADC5)PA5)
ADDR14: IC1.31 ((ADC6)PA6), MID.7
ADDR15: HIGH.11, IC1.30 ((ADC7)PA7)
ADDRB0: LOW.10
ADDRB1: MID.14
ADDRB2: LOW.12
ADDRB3: MID.16
ADDRB4: LOW.14
ADDRB5: HIGH.2
ADDRB6: LOW.16
ADDRB7: HIGH.4
ADDRB8: MID.2
ADDRB9: HIGH.6
ADDRB10: MID.4
ADDRB11: HIGH.8
ADDRB12: MID.6
ADDRB13: HIGH.10
ADDRB14: MID.8
ADDRB15: HIGH.12
DATAA0: IC1.19 (PC0(SCL)), JP2.1
DATAA1: IC1.20 (PC1(SDA)), JP2.2
DATAA2: IC1.21 ((TCK)PC2), JP2.3
DATAA3: IC1.22 ((TMS)PC3), JP2.4
DATAA4: IC1.23 ((TDO)PC4), JP2.5
DATAA5: IC1.24 ((TDI)PC5), JP2.6
DATAA6: IC1.25 ((TOSC1)PC6), JP2.7
DATAA7: IC1.26 ((TOSC2)PC7), JP2.8
DATAB0: IC1.9 ((RXD)PD0), JP3.1
DATAB1: IC1.10 ((TXD)PD1), JP3.2
DATAB2: IC1.11 ((INT0)PD2), JP3.3
DATAB3: IC1.12 ((INT1)PD3), JP3.4
DATAB4: IC1.13 ((OC1B)PD4), JP3.5
DATAB5: IC1.14 ((OC1A)PD5), JP3.6
DATAB6: IC1.15 ((ICP)PD6), JP3.7
DATAB7: IC1.16 ((OC2)PD7), JP3.8
unnamed: IC1.4 (RESET), JP4.2, R1.2
OE: JP1.4
VCC: IC1.5 (VCC), IC1.17 (VCC1), IC1.27 (AVCC), IC1.29 (AREF), IC1.38 (VCC2), JP1.6, JP4.5, R1.1
VDD: IC1.6 (GND), IC1.7 (XTAL2), IC1.8 (XTAL1), IC1.18 (GND1), IC1.28 (GND), IC1.39 (GND2), JP1.5, JP4.1
WE1: JP1.3
WE2: JP1.2

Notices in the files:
P1001-001 - 16bit CPU/P1001-001-005-320 - Controller Flash/SCH1001-001-005-320 - Controller Flash.brd:
Copyright 2019, James Wright
